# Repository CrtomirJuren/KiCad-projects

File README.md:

# KiCad Projects

[TOC]

## Shematics Design Process

### 1 Setup

#### 1 Setup

#### 2 Symbols

#### 3 AAA - arange, annotate, associate

#### 4 Wire

#### 5 Nets

#### 6 Electrical Rules Check

#### 7 Comments

#### 8 Netlist

## PCB Design Process

#### 1 Setup

#### 2 Outline and constraints

#### 3 Place components

#### 4 Route

#### 5 Copper Fillse

#### 6 Design Rules Check

#### 7 Manufacture

7.a) Create Gerber Files

7.b) Create Drill Files

7.c) Validate Files: 

- compress gerber folder
- upload and check: https://www.gerblook.org/

7.d) pcbway OshPark

### Plugins List

#### InteractiveHtmlBom

Create Folder and copy plugin to this directory

```
C:\Users\crtom\AppData\Roaming\kicad\scripting\plugins
```

#### Imgui - KiSymGen

KiSymGen is a cross platform utility enabling users to generate kicad schematic symbols using a graphical tool. KiSymGen is developed based on imgui and GLFW3.

Build On windows.

Tested with visual studio 2017.

- Navigate to the kisymgen folder.

- Double click on the kisymgen.sln file which should open the project in visual studio.

- Build the project and run.

  #### KiCAD Step UP - to use in FreeCAD

## Projects

###	LCD-Rpi3-HAT

-	[Readme](LCD-Rpi3-HAT/readme.md)
-	[Folder](LCD-Rpi3-HAT)
-	[KiCad Project](LCD-Rpi3-HAT/LCD-Rpi3-HAT.pro)

###	Multi-Function-Shield

-	[Readme](Multi-Function-Shield/readme.md)
-	[Folder](Multi-Function-Shield)
-	[KiCad Project](Multi-Function-Shield/Multi-Function-Shield.pro)

###	RaspberryPIFullStackHAT

-	Readme Link
-	KiCad Project Link
-	Folder Link

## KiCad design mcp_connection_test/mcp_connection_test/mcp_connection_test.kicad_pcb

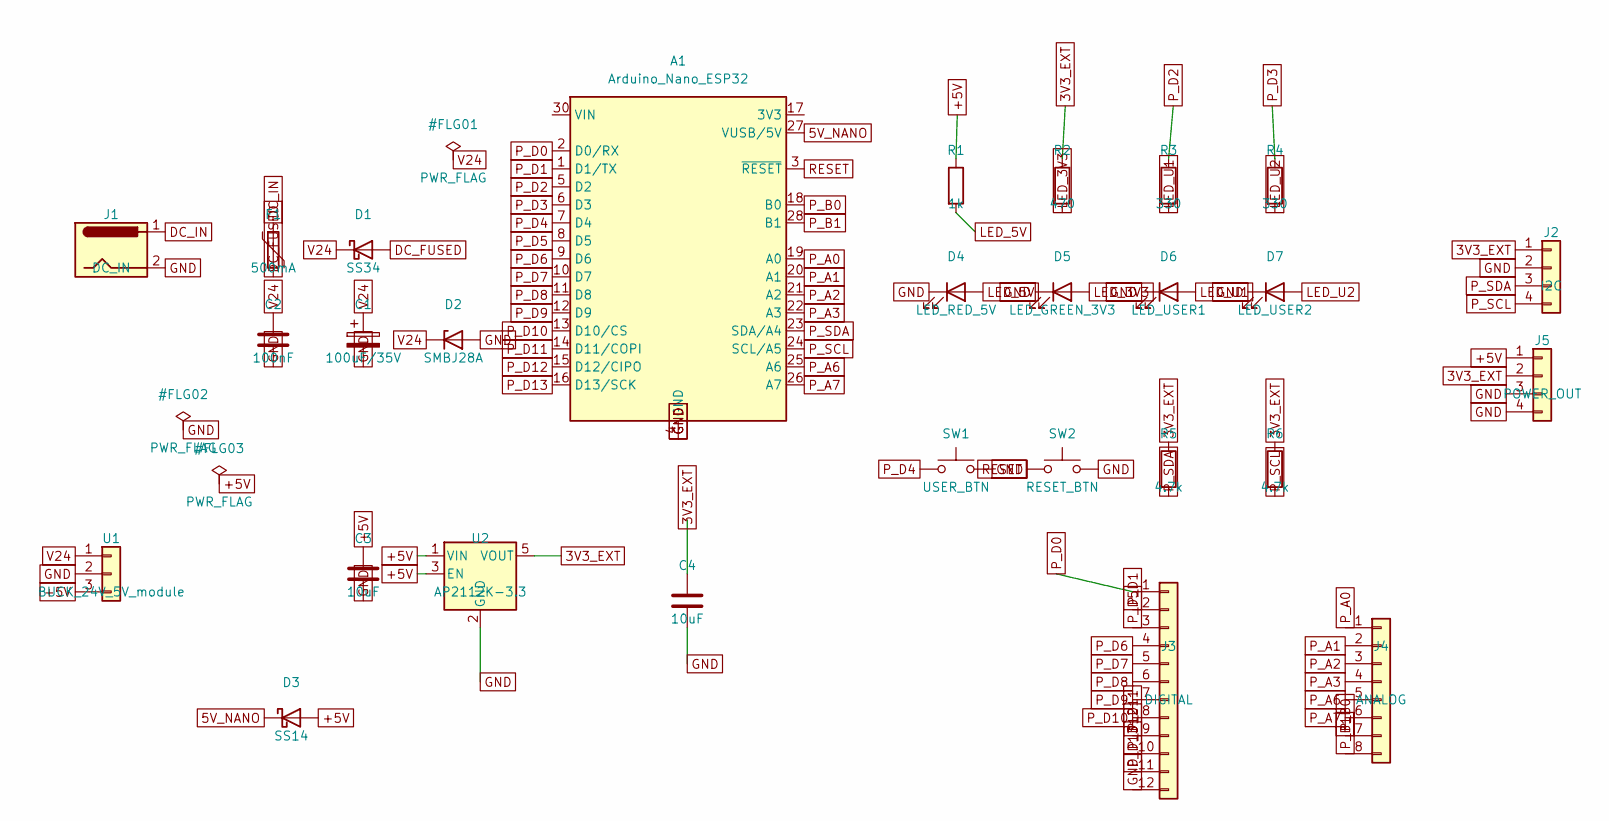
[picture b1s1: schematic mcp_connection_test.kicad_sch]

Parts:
A1: Arduino_Nano_ESP32; Arduino_Nano
C1: 100uF/35V; CP_Radial_D8.0mm_P3.50mm
C2: 100nF; C_0805_2012Metric
C3, C4: 10uF; C_0805_2012Metric
D1: SS34; D_SMA
D2: SMBJ28A; D_SMB
D3: SS14; D_SMA
D4: LED_RED_5V; LED_0805_2012Metric
D5: LED_GREEN_3V3; LED_0805_2012Metric
D6: LED_USER1; LED_0805_2012Metric
D7: LED_USER2; LED_0805_2012Metric
F1: 500mA; Fuse_1812_4532Metric
J1: DC_IN; BarrelJack_Horizontal
J2: I2C; PinHeader_1x04_P2.54mm_Vertical
J3: DIGITAL; PinHeader_1x12_P2.54mm_Vertical
J4: ANALOG; PinHeader_1x08_P2.54mm_Vertical
J5: POWER_OUT; PinHeader_1x04_P2.54mm_Vertical
R1: 1k; R_0805_2012Metric
R2: 470; R_0805_2012Metric
R3, R4: 330; R_0805_2012Metric
R5, R6: 4.7k; R_0805_2012Metric
SW1: USER_BTN; SW_PUSH_6mm
SW2: RESET_BTN; SW_PUSH_6mm
U1: BUCK_24V_5V_module; PinHeader_1x03_P2.54mm_Vertical
U2: AP2112K-3.3; SOT-23-5

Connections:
3V3_EXT: C4.1, J2.1, J5.2, R2.1, R5.1, R6.1, U2.5 (VOUT)
5V_NANO: A1.27 (VUSB/5V), D3.1 (K)
+5V: C3.1, D3.2 (A), J5.1, R1.1, U1.3, U2.1 (VIN), U2.3 (EN)
DC_FUSED: D1.2 (A), F1.2
DC_IN: F1.1, J1.1
GND: A1.4 (GND), A1.29 (GND), C1.2, C2.2, C3.2, C4.2, D2.2 (A), D4.1 (K), D5.1 (K), D6.1 (K), D7.1 (K), J1.2, J2.2, J3.12, J5.3, J5.4, SW1.2, SW2.2, U1.2, U2.2 (GND)
LED_3V3: D5.2 (A), R2.2
LED_5V: D4.2 (A), R1.2
LED_U1: D6.2 (A), R3.2
LED_U2: D7.2 (A), R4.2
P_A0: A1.19 (A0), J4.1
P_A1: A1.20 (A1), J4.2
P_A2: A1.21 (A2), J4.3
P_A3: A1.22 (A3), J4.4
P_A6: A1.25 (A6), J4.5
P_A7: A1.26 (A7), J4.6
P_B0: A1.18 (B0), J4.7
P_B1: A1.28 (B1), J4.8
P_D0: A1.2 (D0/RX), J3.1
P_D1: A1.1 (D1/TX), J3.2
P_D2: A1.5 (D2), R3.1
P_D3: A1.6 (D3), R4.1
P_D4: A1.7 (D4), SW1.1
P_D5: A1.8 (D5), J3.3
P_D6: A1.9 (D6), J3.4
P_D7: A1.10 (D7), J3.5
P_D8: A1.11 (D8), J3.6
P_D9: A1.12 (D9), J3.7
P_D10: A1.13 (D10/CS), J3.8
P_D11: A1.14 (D11/COPI), J3.9
P_D12: A1.15 (D12/CIPO), J3.10
P_D13: A1.16 (D13/SCK), J3.11
P_SCL: A1.24 (SCL/A5), J2.4, R6.2
P_SDA: A1.23 (SDA/A4), J2.3, R5.2
RESET: A1.3 (~RESET), SW2.1
V24: C1.1, C2.1, D1.1 (K), D2.1 (K), U1.1

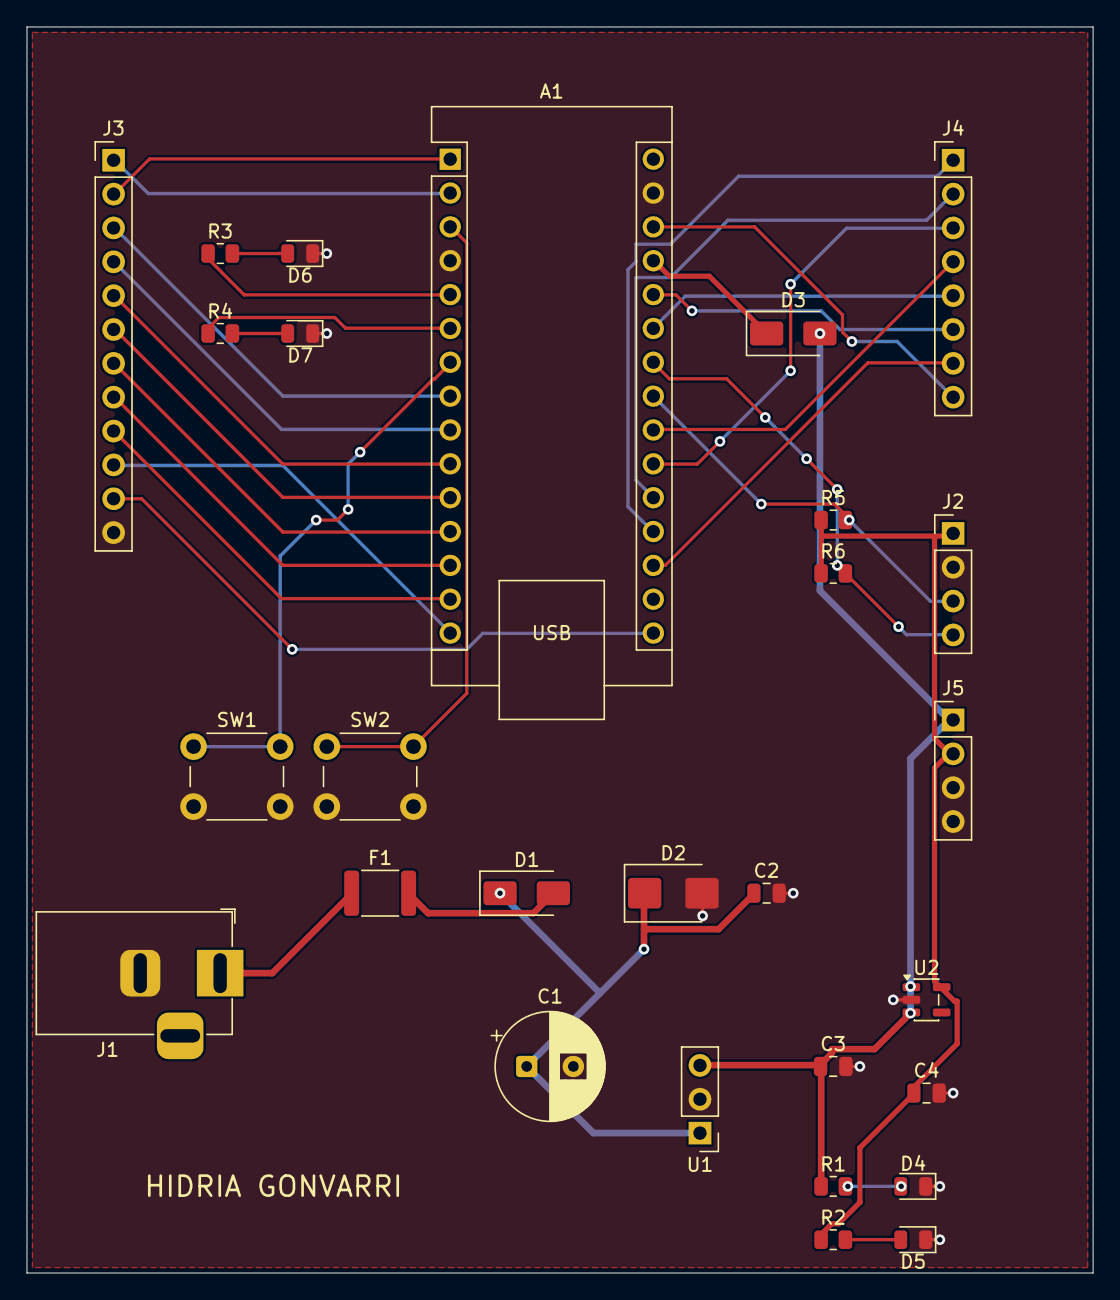
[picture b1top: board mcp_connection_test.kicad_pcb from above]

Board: 2 copper layers, 80.0 x 93.5 mm, 28 parts (0 on the bottom side), 36 nets.

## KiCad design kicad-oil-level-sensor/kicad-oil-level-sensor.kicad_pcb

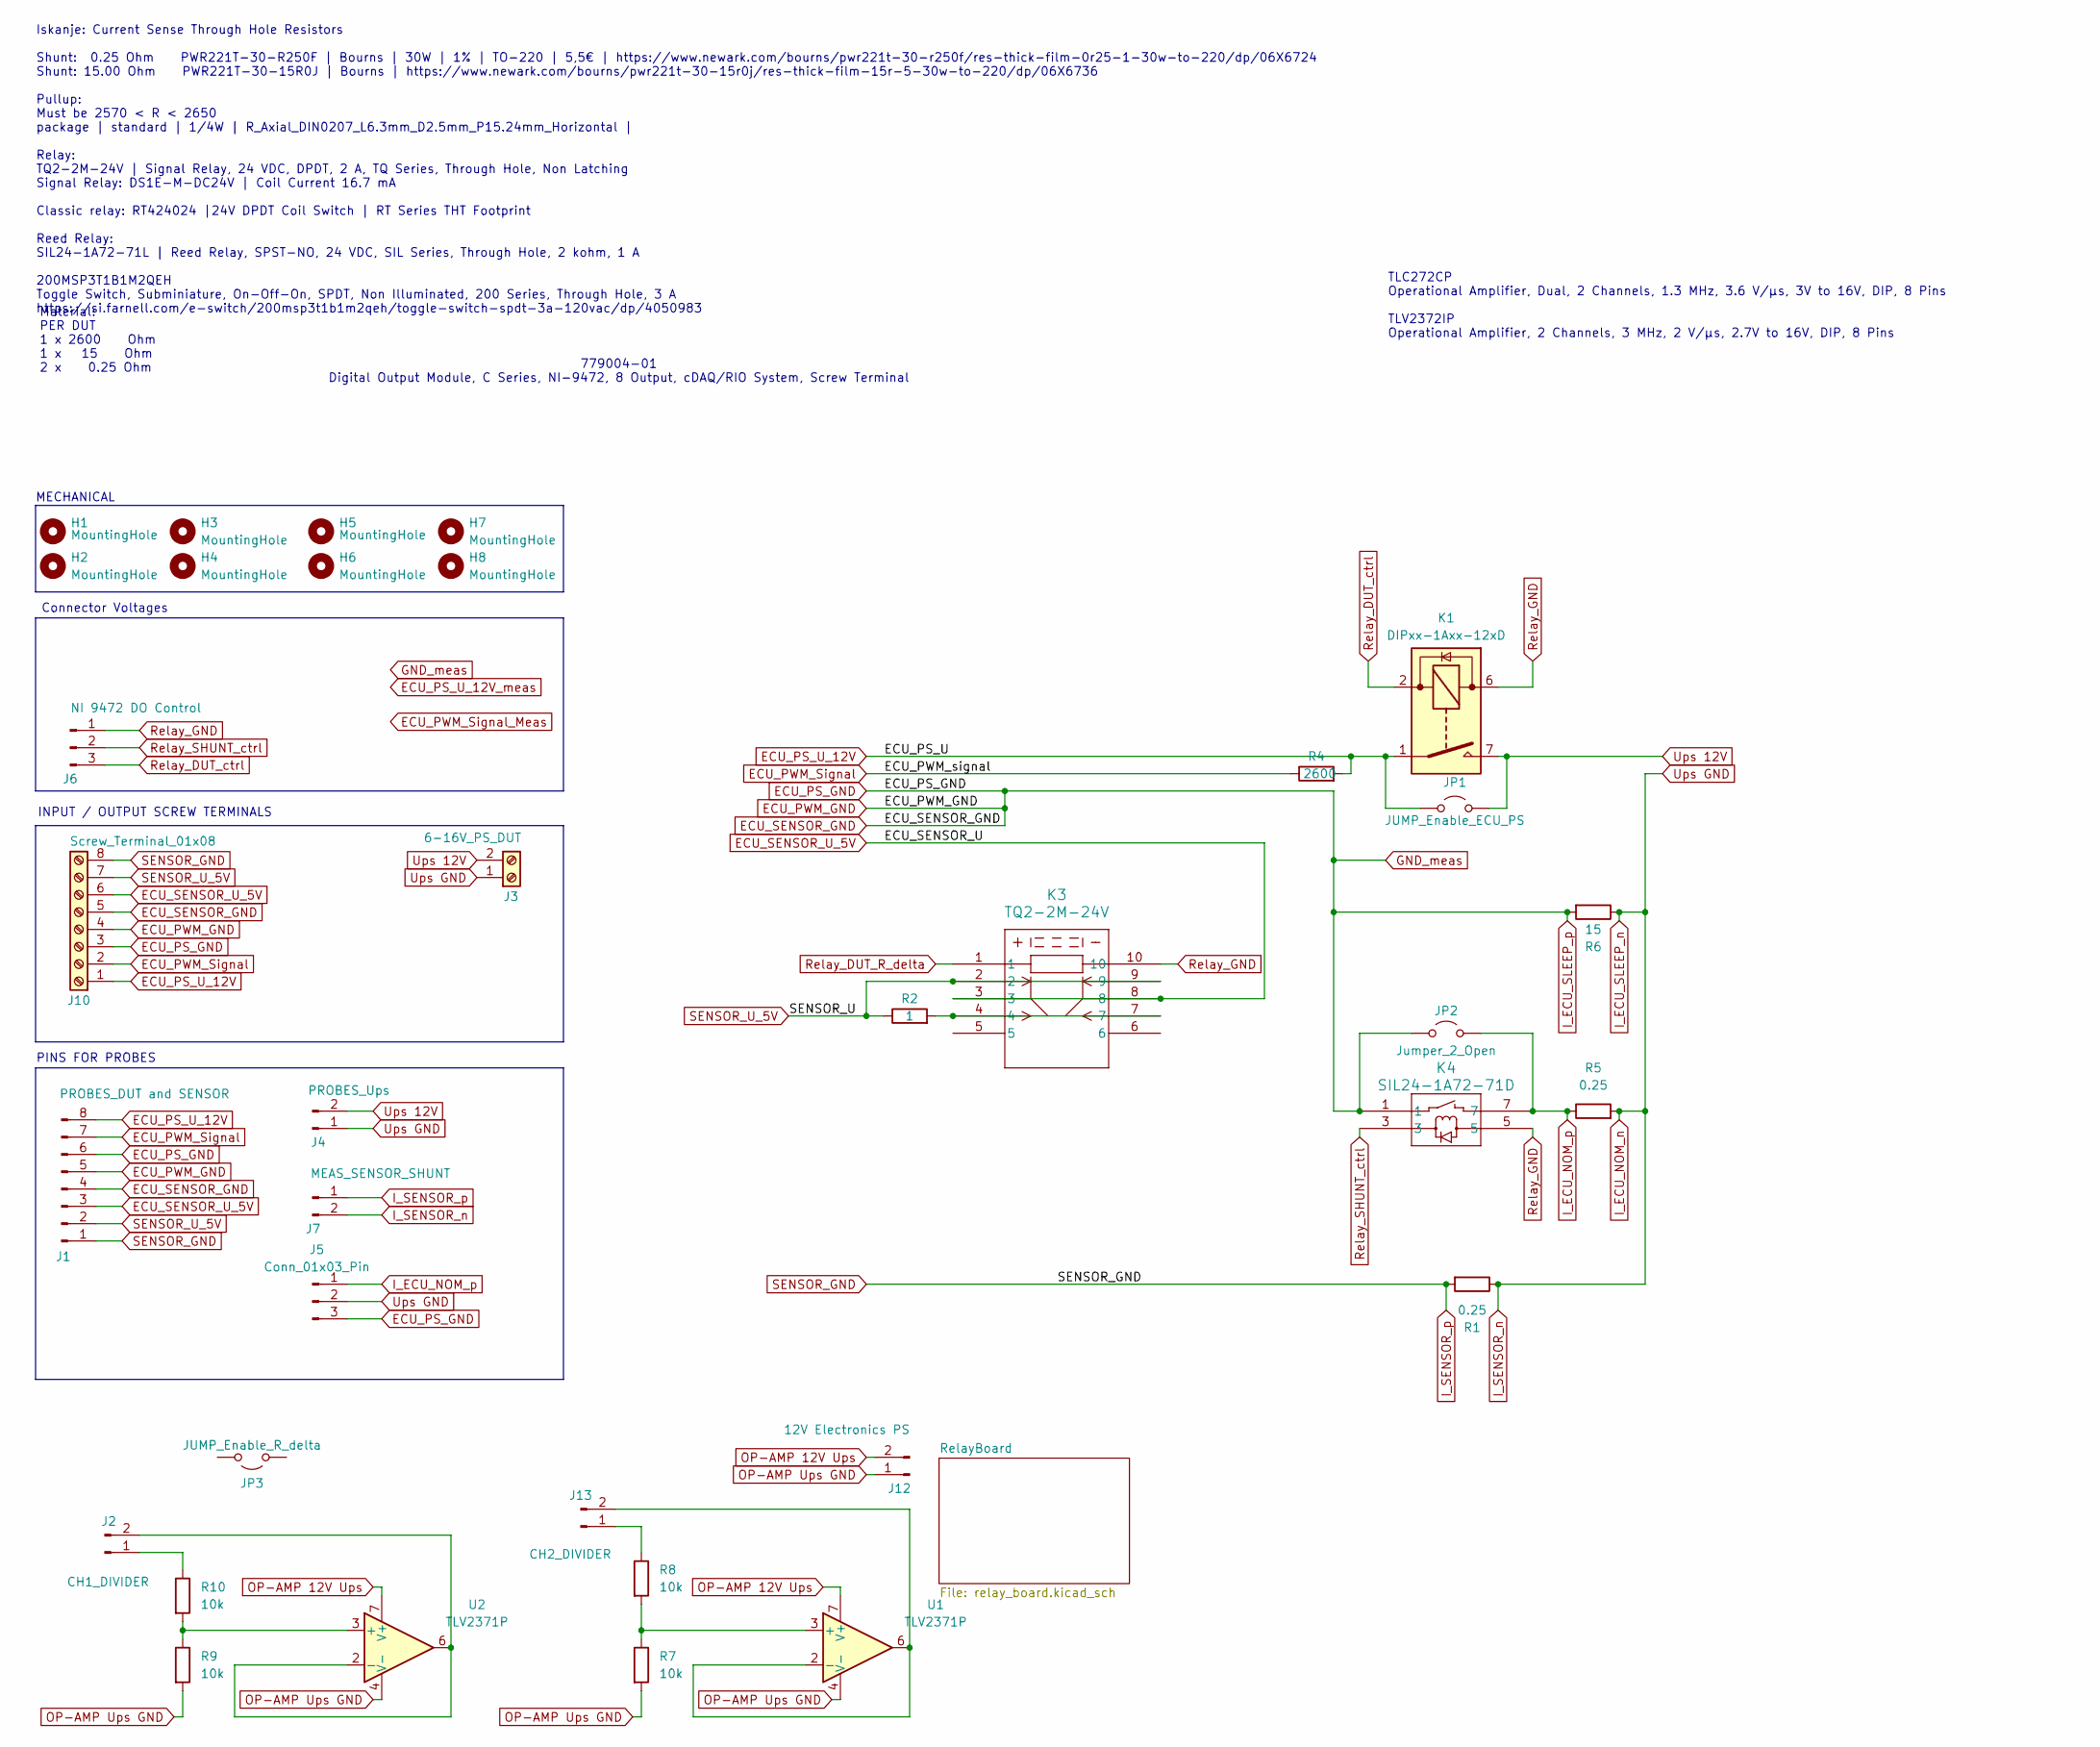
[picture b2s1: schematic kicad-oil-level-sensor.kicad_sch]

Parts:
H1, H2, H3, H4, H5, H6, H7, H8: MountingHole; MountingHole_3.2mm_M3
J1: PROBES_DUT and SENSOR; Samtec_HPM-08-01-x-S_Straight_1x08_Pitch5.08mm
J2: CH1_DIVIDER; Samtec_HPM-02-01-x-S_Straight_1x02_Pitch5.08mm
J3: 6-16V_PS_DUT; TerminalBlock_Phoenix_MKDS-1,5-2-5.08_1x02_P5.08mm_Horizont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
J4: PROBES_Ups; Samtec_HPM-02-01-x-S_Straight_1x02_Pitch5.08mm
J5: Conn_01x03_Pin; Samtec_HPM-03-01-x-S_Straight_1x03_Pitch5.08mm
J6: NI 9472 DO Control; Samtec_HPM-03-01-x-S_Straight_1x03_Pitch5.08mm
J7: MEAS_SENSOR_SHUNT; Samtec_HPM-02-01-x-S_Straight_1x02_Pitch5.08mm
J10: Screw_Terminal_01x08; TerminalBlock_Phoenix_MKDS-3-8-5.08_1x08_P5.08mm_Horizontal
J12: 12V Electronics PS; Samtec_HPM-02-01-x-S_Straight_1x02_Pitch5.08mm
J13: CH2_DIVIDER; Samtec_HPM-02-01-x-S_Straight_1x02_Pitch5.08mm
JP1: JUMP_Enable_ECU_PS; Samtec_HPM-02-01-x-S_Straight_1x02_Pitch5.08mm
JP2: Jumper_2_Open; Samtec_HPM-02-01-x-S_Straight_1x02_Pitch5.08mm
JP3: JUMP_Enable_R_delta; Samtec_HPM-02-01-x-S_Straight_1x02_Pitch5.08mm
K1: DIPxx-1Axx-12xD; Relay_StandexMeder_DIP_LowProfile
K3: TQ2-2M-24V; RELAY10_TQ2-2M_PAN
K4: SIL24-1A72-71D; SIL24-1A72-71D_SDX
R1, R5: 0.25; TO-220-2_Vertical
R2: 1; R_Axial_DIN0207_L6.3mm_D2.5mm_P15.24mm_Horizontal
R4: 2600; R_Axial_DIN0207_L6.3mm_D2.5mm_P15.24mm_Horizontal
R6: 15; TO-220-2_Vertical
R7, R8, R9, R10: 10k; R_Axial_DIN0207_L6.3mm_D2.5mm_P15.24mm_Horizontal
U1, U2: TLV2371P; DIP-8_W7.62mm

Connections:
ECU_PS_GND: J1.4, J1.5, J1.6, J5.3, J10.3, J10.4, J10.5, JP2.1 (A), K4.1, R6.2
ECU_PS_U_12V: J1.8, J10.1, JP1.1 (A), K1.1, K1.14, R4.2
ECU_PWM_Signal: J1.7, J10.2, R4.1
ECU_SENSOR_U_5V: J1.3, J10.6, K3.3, K3.8
I_ECU_NOM_n: J3.1, J4.1, J5.2, J7.2, R1.1, R5.2, R6.1
I_ECU_NOM_p: J5.1, JP2.2 (B), K4.7, R5.1
I_SENSOR_p: J1.1, J7.1, J10.8, R1.2
unnamed: J2.1, R10.1
unnamed: J2.2, U2.2 (-), U2.6
unnamed: J13.1, R8.1
unnamed: J13.2, U1.2 (-), U1.6
unnamed: K3.4, K3.7, R2.2
unnamed: R7.1, R8.2, U1.3 (+)
unnamed: R9.1, R10.2, U2.3 (+)
OP-AMP 12V Ups: J12.2, U1.7 (V+), U2.7 (V+)
OP-AMP Ups GND: J12.1, R7.2, R9.2, U1.4 (V-), U2.4 (V-)
Relay_DUT_R_delta: K3.1
Relay_DUT_ctrl: J6.3, K1.2, K1.13
Relay_GND: J6.1, K1.6, K3.10, K4.5
Relay_SHUNT_ctrl: J6.2, K4.3
SENSOR_U_5V: J1.2, J10.7, K3.2, K3.9, R2.1
Ups 12V: J3.2, J4.2, JP1.2 (B), K1.7, K1.8

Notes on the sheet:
779004-01 Digital Output Module, C Series, NI-9472, 8 Output, cDAQ/RIO System, Screw Terminal
INPUT / OUTPUT SCREW TERMINALS
TLC272CP Operational Amplifier, Dual, 2 Channels, 1.3 MHz, 3.6 V/µs, 3V to 16V, DIP, 8 Pins TLV2372IP Operational Amplifier, 2 Channels, 3 MHz, 2 V/µs, 2.7V to 16V, DIP, 8 Pins
Iskanje: Current Sense Through Hole Resistors Shunt: 0.25 Ohm PWR221T-30-R250F | Bourns | 30W | 1% | TO-220 | 5,5€ | https://www.newark.com/bourns/pwr221t-30-r250f/res-thick-film-0r25-1-30w-to-220/dp/06X6724 Shunt: 15.00 Ohm PWR221T-30-15R0J | Bourns | https://www.newark.com/bourns/pwr221t-30-15r0j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
PINS FOR PROBES
Connector Voltages
Material: PER DUT 1 x 2600 Ohm 1 x 15 Ohm 2 x 0.25 Ohm
MECHANICAL

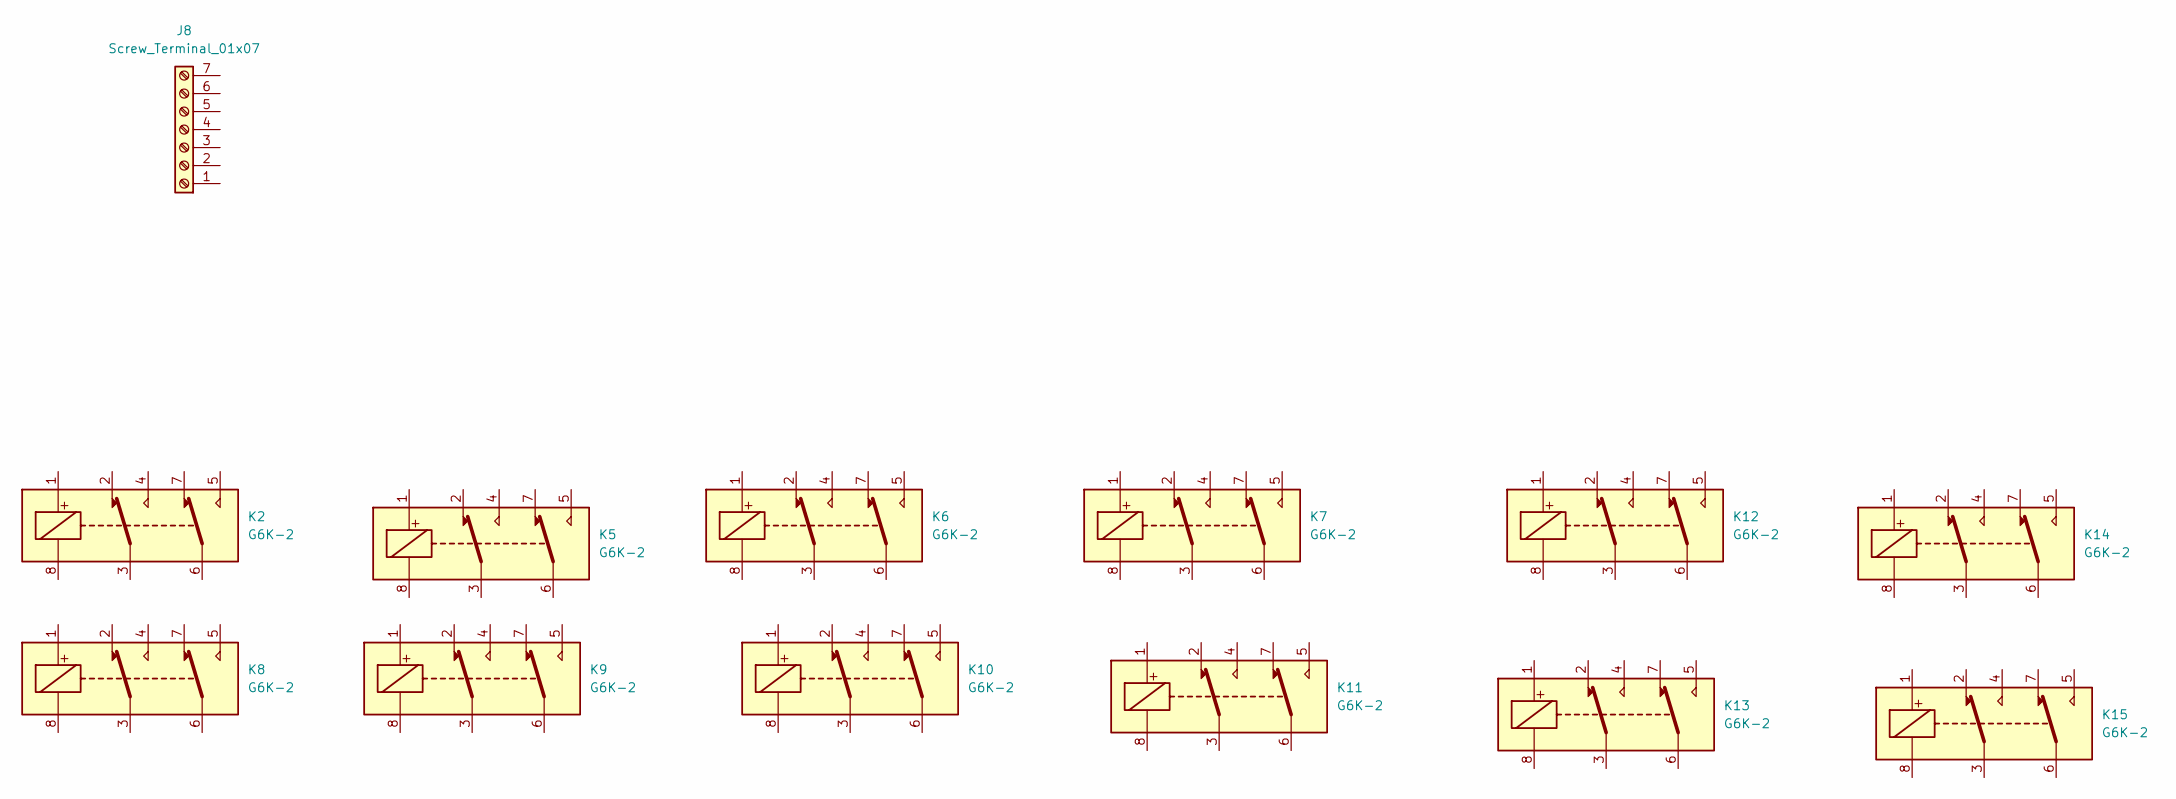
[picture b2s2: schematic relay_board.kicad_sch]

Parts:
J8: Screw_Terminal_01x07
K2, K5, K6, K7, K8, K9, K10, K11, K12, K13, K14, K15: G6K-2; Relay_DPDT_Omron_G6K-2P

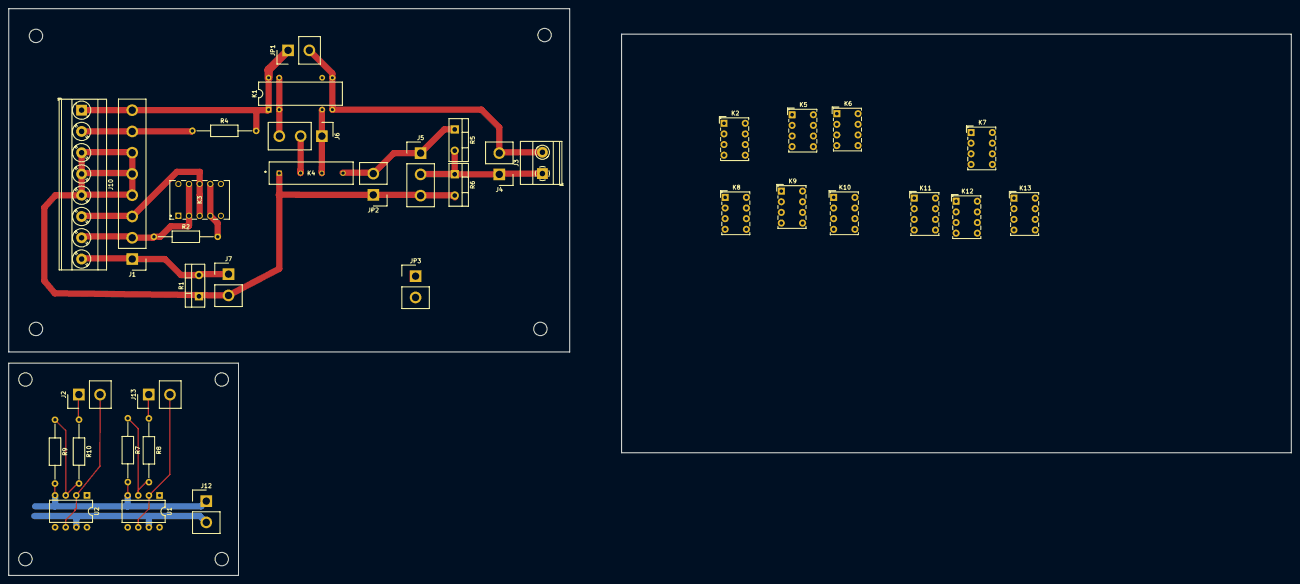
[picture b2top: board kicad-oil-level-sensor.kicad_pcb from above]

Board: 2 copper layers, 306.4 x 135.4 mm, 45 parts (0 on the bottom side), 21 nets.

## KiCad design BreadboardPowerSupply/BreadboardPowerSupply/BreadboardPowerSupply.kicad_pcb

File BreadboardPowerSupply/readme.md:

#	Breadboard Power Supply - KiCadLikeAPro

| Date       | Version | Comment                         |
| ---------- | ------- | ------------------------------- |
| 2020-10-18 | v1      | kicad like a pro udemy learning |

##	Info

Double-sided PCB for a 5V power supply. You will be able to use this power supply to power your breadboard Arduino projects, or any project that requires a 5V power supply. As an input
to your power supply, you can use an old DC or AC walled power supply, as long as its output voltage does 

Input voltage: 6V - 35V

Output voltage: 5V

## Shematics - EESchema

## Physical Dimensions

Breadboard Dimensions: 84mm *  55mm 

PCB dimensions: 52,070mm* 30,48mm

##	PCB - Pcbnew

##	3D View

## Bill of Materials - BOM

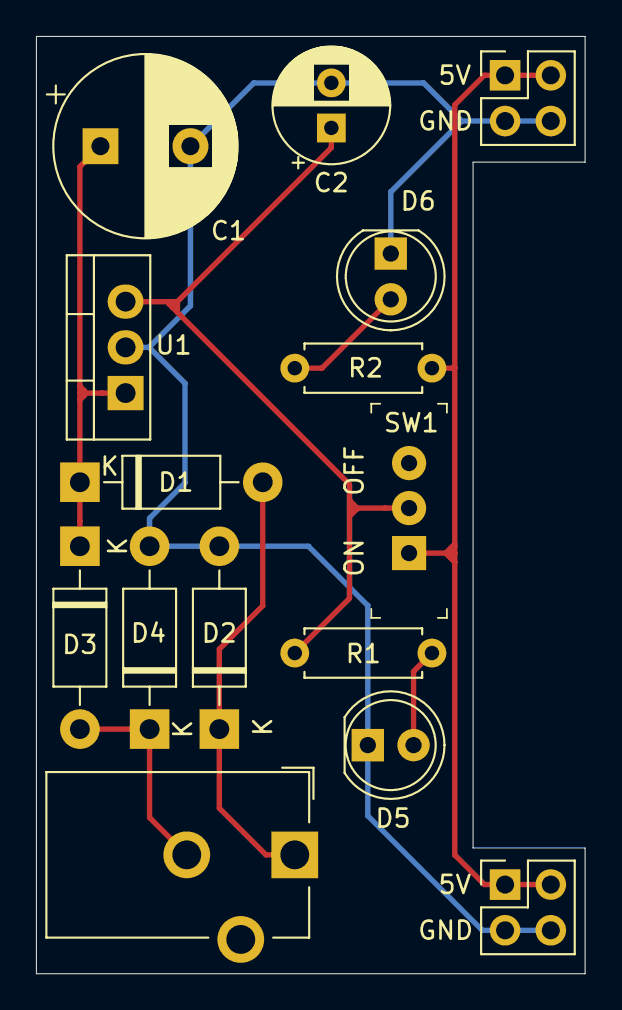
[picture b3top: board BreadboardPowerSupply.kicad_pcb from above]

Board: 2 copper layers, 30.5 x 52.1 mm, 12 parts (0 on the bottom side), 8 nets.

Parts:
C1: CP; CP_Radial_D10.0mm_P5.00mm
C2: CP; CP_Radial_D6.3mm_P2.50mm
D1, D2, D3, D4: 1N4007; D_DO-41_SOD81_P10.16mm_Horizontal
D5, D6: LED; LED_D5.0mm
R1, R2: R; R_Axial_DIN0207_L6.3mm_D2.5mm_P7.62mm_Horizontal
SW1: SW_DPDT_x2; Switch_Slide_11.6x4mm_EG1218
U1: LM7805_TO220; TO-220-3_Vertical

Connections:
/V-: C1.2, C2.2, D2.2, D4.2, D5.1, D6.1, U1.2
/Vin: C1.1, D1.1, D3.1, U1.1
/Vout1: C2.1, R1.2, SW1.2, U1.3
/Vout2: R2.2, SW1.1
unnamed: D1.2, D2.1
unnamed: D3.2, D4.1
unnamed: D5.2, R1.1
unnamed: D6.2, R2.1

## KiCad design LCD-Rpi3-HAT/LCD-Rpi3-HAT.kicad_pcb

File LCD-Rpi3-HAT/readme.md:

#	LCD-Rpi3-HAT

##	Project info

-	Raspberry 3 HAT
-	IO pin expander MCP23017-E_sp
-	5 buttons: L,R,U,D, Enter
-	3 led indicator
-	LCD 4bit data

##	IO Expander MCP23017 Pinout

-	i2c address = 0x20(all jumpers NC = 000)

| MCP23017 	| Function 	|
|----------	|----------	|
| GPA0     	| NC       	|
| GPA1     	| LCD_RS   	|
| GPA2     	| LCD_RW   	|
| GPA3     	| LCD_E    	|
| GPA4     	| LCD_D4   	|
| GPA5     	| LCD_D5   	|
| GPA6     	| LCD_D6   	|
| GPA7     	| LCD_D7   	|

| MCP23017 	| Function       	|
|----------	|----------------	|
| GPB0     	| button-2-down  	|
| GPB1     	| button-5-enter 	|
| GPB2     	| button-4-right 	|
| GPB3     	| button-1-up    	|
| GPB4     	| button-3-left  	|
| GPB5     	| led-1-green    	|
| GPB6     	| led-2-yellow   	|
| GPB7     	| led-3-red      	|

##	Eeschema

##	Pcbnew

##	3D View

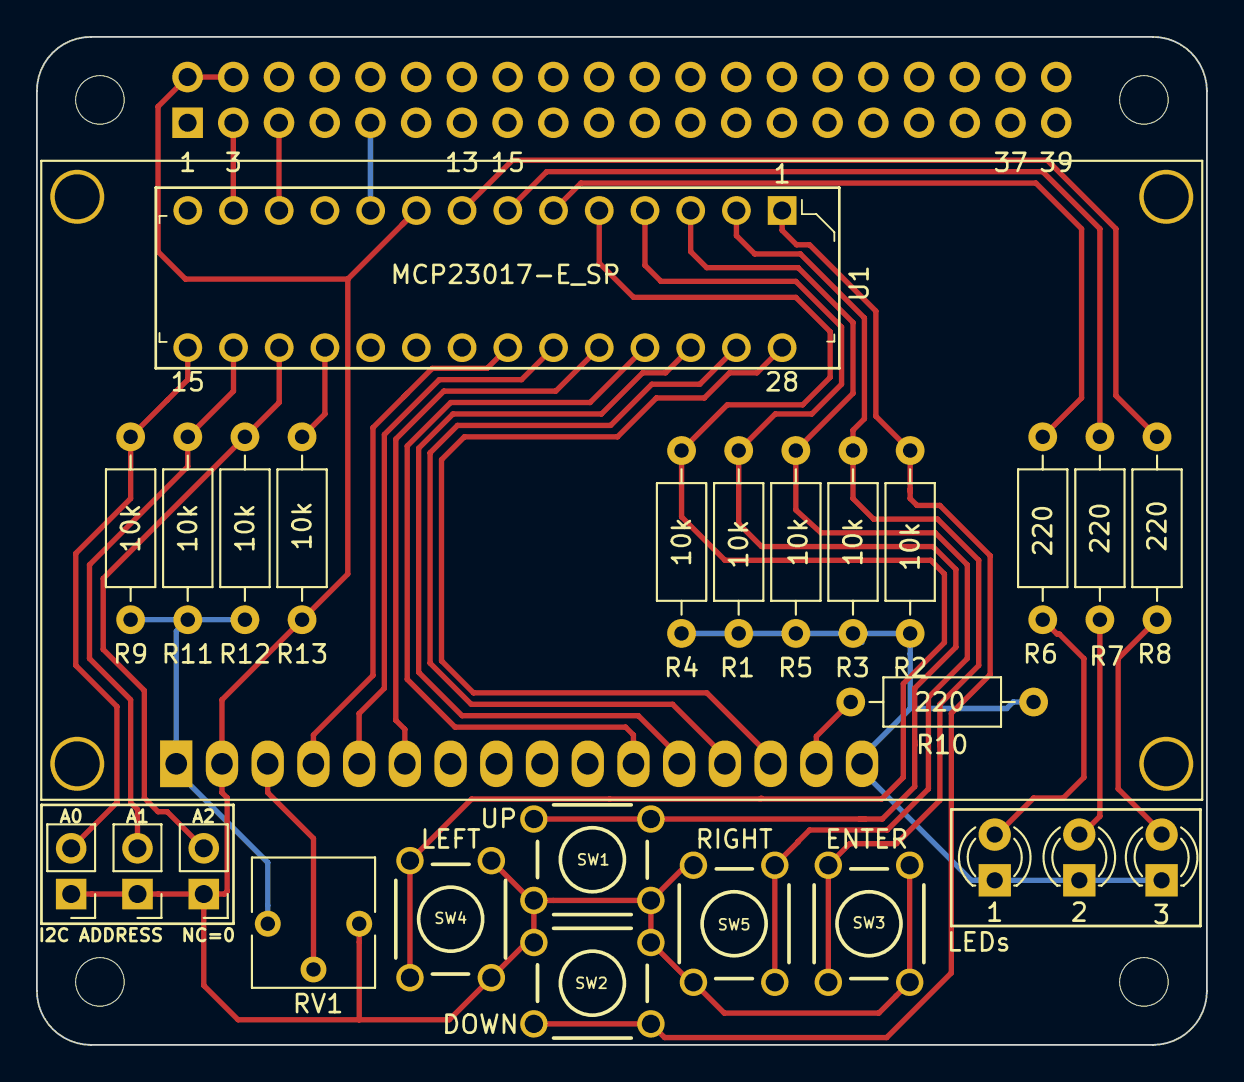
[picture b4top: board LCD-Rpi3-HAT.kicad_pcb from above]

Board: 2 copper layers, 65.0 x 56.0 mm, 32 parts (1 on the bottom side), 29 nets.

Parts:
1, 2, 3: LED; LED_D3.0mm
A0, A1, A2: Jumper_NC_Small; PinHeader_1x02_P2.54mm_Vertical
DS1: WC1602A; LCD_16X2_MC21605H6WK
MK1, MK2, MK3, MK4: M2.5; MountingHole_2.7mm_M2.5
P1: Conn_02x20_Odd_Even; PinSocket_2x20_P2.54mm_Vertical
R1, R2, R3, R4, R5, R9, R11, R12, R13: 10k; R_Axial_DIN0207_L6.3mm_D2.5mm_P10.16mm_Horizontal
R6, R7, R8, R10: 220; R_Axial_DIN0207_L6.3mm_D2.5mm_P10.16mm_Horizontal
RV1: 10k; Potentiometer_Vishay_T73YP_Vertical
SW1: SW_up; SW_PUSHBUTTON_PTH
SW2: SW_down; SW_PUSHBUTTON_PTH
SW3: SW_enter; SW_PUSHBUTTON_PTH
SW4: SW_left; SW_PUSHBUTTON_PTH
SW5: SW_right; SW_PUSHBUTTON_PTH
U1: MCP23017-E_SP; DIP-28_W7.62mm

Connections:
+3V3: P1.1, P1.17
+5V: A0.1, A1.1, A2.1, DS1.2, P1.2, P1.4, R13.1, RV1.3, SW1.1, SW2.1, SW3.1, SW4.1, SW5.1, U1.9
/GPIO2(SDA1): P1.3, U1.13
/GPIO3(SCL1): P1.5, U1.12
/LCD_D4: DS1.11, U1.25
/LCD_D5: DS1.12, U1.26
/LCD_D6: DS1.13, U1.27
/LCD_D7: DS1.14, U1.28
/LCD_E: DS1.6, U1.24
/LCD_RS: DS1.4, U1.22
/LCD_RW: DS1.5, U1.23
/button_1_up: R1.1, SW1.2, U1.4
/button_2_down: R2.1, SW2.2, U1.1
/button_3_left: R4.1, SW4.2, U1.5
/button_4_right: R5.1, SW5.2, U1.3
/button_5_enter: R3.1, SW3.2, U1.2
/led_1_green: R6.1, U1.6
/led_2_yellow: R7.1, U1.7
/led_3_red: R8.1, U1.8
GND: 1.1, 2.1, 3.1, DS1.1, DS1.16, P1.6, P1.9, P1.14, P1.20, P1.25, P1.30, P1.34, P1.39, R1.2, R2.2, R3.2, R4.2, R5.2, R9.2, R10.1, R11.2, R12.2, RV1.1, U1.10
unnamed: 1.2, R6.2
unnamed: 2.2, R7.2
unnamed: 3.2, R8.2
unnamed: DS1.3, RV1.2
unnamed: DS1.15, R10.2
unnamed: A0.2, R9.1, U1.15
unnamed: A1.2, R11.1, U1.16
unnamed: A2.2, R12.1, U1.17
unnamed: R13.2, U1.18

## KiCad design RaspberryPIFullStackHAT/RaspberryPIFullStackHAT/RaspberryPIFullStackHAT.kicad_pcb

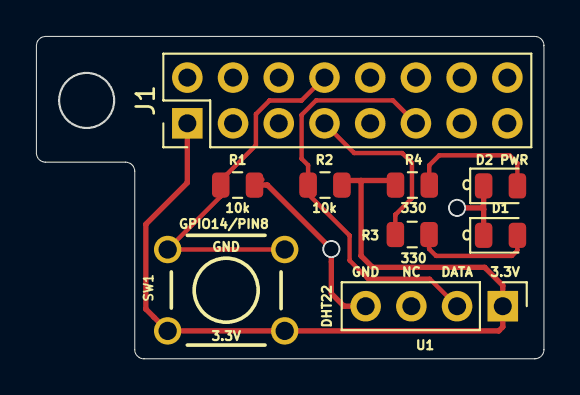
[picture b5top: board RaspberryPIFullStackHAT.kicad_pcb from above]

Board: 2 copper layers, 28.2 x 17.9 mm, 9 parts (0 on the bottom side), 7 nets.

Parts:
D1, D2: LED; LED_0805_2012Metric
J1: Raspberry_Pi_2_3; PinHeader_2x08_P2.54mm_Vertical
R1, R2: 10k; R_0805_2012Metric
R3, R4: 330; R_0805_2012Metric
SW1: SW_DPST; SW_PUSHBUTTON_PTH
U1: DHT22; PinHeader_1x04_P2.54mm_Vertical

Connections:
+3V3: J1.1, R2.1, R4.2, SW1.1, U1.1
/DHT22_input: J1.11, R2.2, U1.2
/button_input: J1.8, R1.2, SW1.2
/led_output: J1.7, R3.2
GND: D1.1, D2.1, J1.6, J1.9, R1.1, U1.4
unnamed: D1.2, R3.1
unnamed: D2.2, R4.1

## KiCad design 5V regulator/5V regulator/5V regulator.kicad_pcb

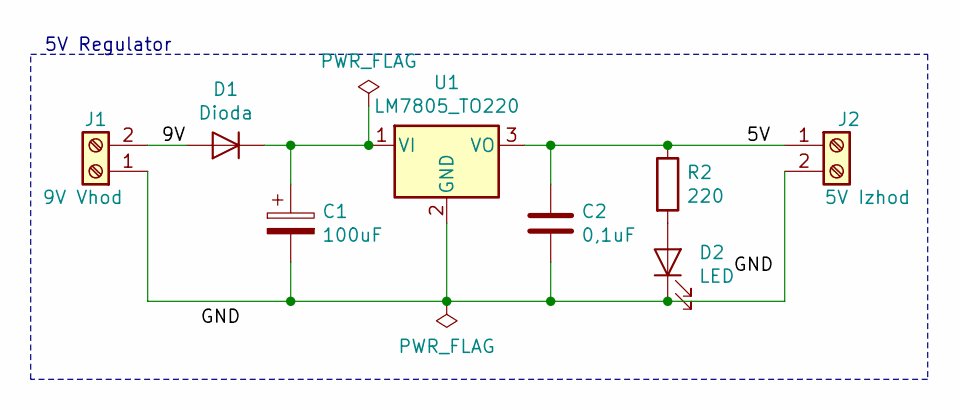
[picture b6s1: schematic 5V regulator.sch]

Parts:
C1: 100uF; CP_Radial_D8.0mm_P3.50mm
C2: 0,1uF; C_Rect_L7.0mm_W2.5mm_P5.00mm
D1: Dioda; D_DO-41_SOD81_P10.16mm_Horizontal
D2: LED; LED_D3.0mm
J1: 9V Vhod; TerminalBlock_bornier-2_P5.08mm
J2: 5V Izhod; TerminalBlock_bornier-2_P5.08mm
R2: 220; R_Axial_DIN0207_L6.3mm_D2.5mm_P10.16mm_Horizontal
U1: LM7805_TO220; TO-220-3_Vertical

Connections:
/5V: C2.1, J2.1, R2.1, U1.3 (VO)
/9V: D1.2 (A), J1.2
unnamed: C1.1, D1.1 (K), U1.1 (VI)
unnamed: C1.2, C2.2, D2.1 (K), J1.1, J2.2, U1.2 (GND)
unnamed: D2.2 (A), R2.2

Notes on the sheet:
5V Regulator

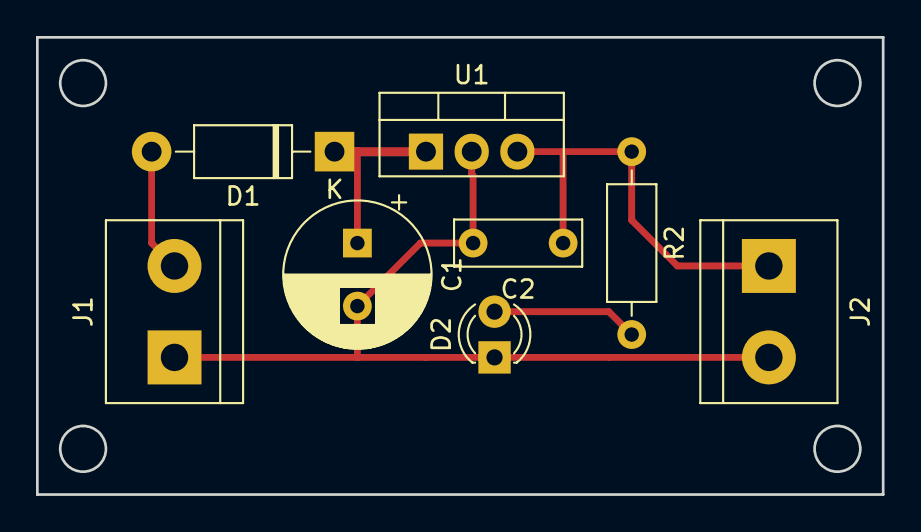
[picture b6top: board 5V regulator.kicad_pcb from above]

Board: 2 copper layers, 47.0 x 25.4 mm, 8 parts (0 on the bottom side), 5 nets.

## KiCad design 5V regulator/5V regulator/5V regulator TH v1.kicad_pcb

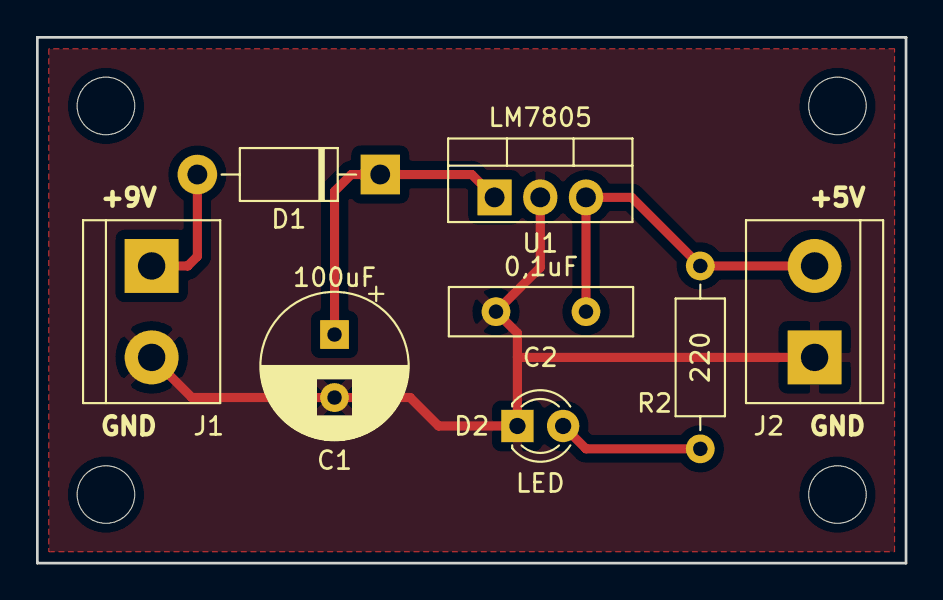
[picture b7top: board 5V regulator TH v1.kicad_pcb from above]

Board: 2 copper layers, 48.3 x 29.2 mm, 8 parts (0 on the bottom side), 5 nets.

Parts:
C1: 100uF; CP_Radial_D8.0mm_P3.50mm
C2: 0,1uF; C_Disc_D10.0mm_W2.5mm_P5.00mm
D1: Dioda; D_DO-41_SOD81_P10.16mm_Horizontal
D2: LED; LED_D3.0mm
J1: 9V Vhod; TerminalBlock_bornier-2_P5.08mm
J2: 5V Izhod; TerminalBlock_bornier-2_P5.08mm
R2: 220; R_Axial_DIN0207_L6.3mm_D2.5mm_P10.16mm_Horizontal
U1: LM7805; TO-220-3_Vertical

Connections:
/5V: C2.1, J2.2, R2.1, U1.3
/9V: D1.2, J1.1
/GND: C1.2, C2.2, D2.1, J1.2, J2.1, U1.2
unnamed: C1.1, D1.1, U1.1
unnamed: D2.2, R2.2

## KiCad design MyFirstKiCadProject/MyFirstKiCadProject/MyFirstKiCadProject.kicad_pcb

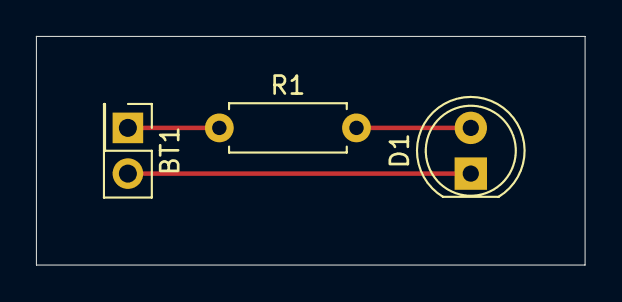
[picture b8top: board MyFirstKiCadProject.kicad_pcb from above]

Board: 2 copper layers, 30.5 x 12.7 mm, 3 parts (0 on the bottom side), 3 nets.

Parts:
BT1: 9V; PinHeader_2x01_P2.54mm_Vertical
D1: LED; LED_D5.0mm
R1: 470; R_Axial_DIN0207_L6.3mm_D2.5mm_P7.62mm_Horizontal

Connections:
unnamed: BT1.1, R1.1
unnamed: BT1.2, D1.1
unnamed: D1.2, R1.2

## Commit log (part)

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2019-11-07 first commit from work - preko mobi dostopne točke
2019-11-07 5v regulator pcb
2019-11-08 updated 5v regulator
2019-11-17 update doma
2019-11-17 added ir led array
2019-11-17 removed robosled modules
2019-12-01 added project template
2019-12-01 breadboard power supply
2019-12-05 start on raspberry pi hat
2019-12-08 work on raspberry pi hat
2019-12-10 no message
2020-01-02 main readme updated, LCD RPI3 HAT updated
